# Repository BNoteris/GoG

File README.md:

# LoRa GPS IoT — PCB Proof-of-Concept

This repository hosts the LoRa GPS IoT proof-of-concept developed as the final project of the High Frequency Circuit Design course at ECAM.
The system integrates a GPS receiver, an ESP32 microcontroller, and a LoRa transceiver to provide location reporting over the LoRaWAN 868 MHz band.
A dedicated custom PCB antenna was designed, simulated and produced for LoRa operation at 868 MHz 
The design was specified in collaboration with an industrial partner and implemented on a 2‑layer FR4 PCB.
Every tool used during this project was open-source.

<div align="center">

</div>

All KiCad & gerber files are available in the [hardware](/hardware) directory.

Antenna simulation can be found in [software](/software).

## Specifications

- Provide GPS-based localization transmission over LoRa at the 868 MHz European LoRa frequency band.
- Support Wi-Fi/BLE communication with ESP32 provided antenna.
- Support multiple power inputs: USB‑C, external battery (2S), and solar panel input.
- Create a compact PCB (≤ 10×10 cm for fabrication on JLCPCB) as a proof of concept.
- Create a custom Inverted‑F Antenna (IFA) tuned to 868 MHz.

## Hardware used

- **ESP32‑C3‑WROOM‑02** — main MCU (USB‑C programming and Wi‑Fi/BLE). Supports SPI and I²C for peripheral interfaces.
- **RFM95 (LoRa) module** — 868 MHz LoRa transceiver (module used without on‑board antenna; external/custom antenna on separate antenna PCB).
- **GPS module AM‑M8Q‑0** — GNSS receiver for latitude/longitude acquisition.
- **BQ25798** — battery charger/power manager supporting USB‑C and solar inputs, designed for a 2S battery configuration.
- **USB‑C connector** — for programming and charging.
- **SMA connector** — RF connector for the custom antenna / external antenna.

## Antenna simulation & testing
### Simulation

Electromagnetic simulations were performed using the Emerge Python‑based EM tool to optimize the antenna geometry for maximum radiated power and minimal reflection at the target frequency.

 | 
:------------:|:--------------------------:
S11 reflection coefficient | Smith chart of reflection coefficient

Primary performance metrics from simulation:
- Minimum simulated **S₁₁ = −17.75 dB at 868 MHz**.
- **−10 dB impedance bandwidth ≈ 50 MHz**, which covers the LoRaWAN band with margin for manufacturing tolerances.

The simulated Smith chart shows the antenna impedance close to the center (near 50 Ω) at 868 MHz; minor adjustments were left open to address real‑world feed/feedline/environment effects.

 | 
:-----------:|:-------------------:
Far-Field E  |  Polar Far-Field E

<div align="center">

</div>

Far‑field results (normalized E‑field, polar plots and 3D radiation pattern) were generated to verify radiation behaviour

### Hardware validation

<div align="center">

</div>

The manufactured IFA PCB was integrated into the system and validated using a Digital Spectrum Analyzer (DSA) by observing a distinct spectral peak at 868 MHz aligned with the transmission cadence when our custom antenna is sending its packet to a reference antenna tuned to the same band.

 | 
:-------------------------------------------------:|:---------------------------------------------:
Spectrum analysis without custom antenna emission  | Spectrum analysis with custom antenna emission 

Results confirm that the antenna radiates at the intended operating frequency.
Minor nearby spectral peaks were attributed to ambient RF activity.

Limitations: a Vector Network Analyzer (VNA) was not available during testing, preventing direct measurement of the antenna reflection coefficient (S₁₁) on the manufactured part.
This measurement is recommended for a definitive comparison against simulation.

## Improvements

Several enhancements could be considered to further improve the system’s performance 
and quality: 
- As the PCB was intentionally designed with only 2 layers and no ground/power 
planes to observe and measure EMI, but has finally not been done, upgrading our 
design to 4 layers with copper planes would simplify the PCB layout and improve 
EMC. It would, consequently, allow for a more compact design, making it more 
practical.
- Testing our system to EMI interferences would allow to have a better knowledge of 
its real-world performance, as well as its capability to respect HF regulations, a 
mandatory step to deliver our product to the market. 
- Access to a Vector Network Analyzer (or even a LiteVNA) would enable precise 
measurements of the antenna reflection coefficient and matching impedance, 
allowing direct comparison with simulation results and more accurate impedance 
tuning. 
- Testing the system in a real-world environment would provide more information on 
its robustness, in particular, packet loss and communication range and 
performance.

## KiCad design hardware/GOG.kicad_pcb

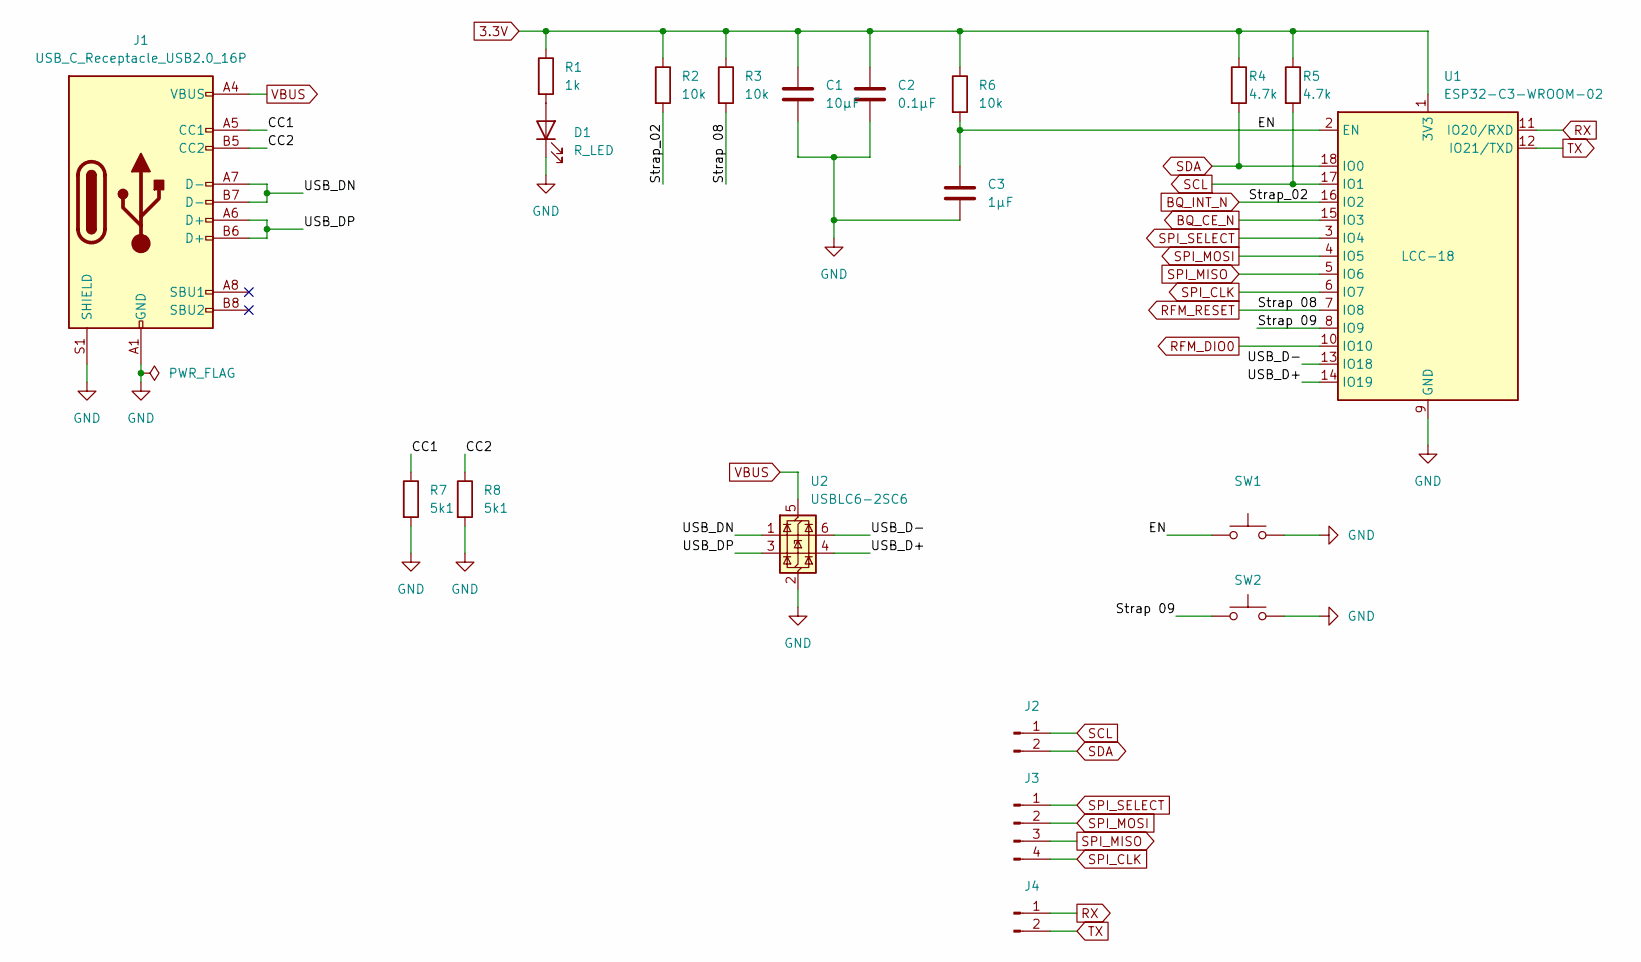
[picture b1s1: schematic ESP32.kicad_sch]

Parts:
C1: 10µF; C_0603_1608Metric; JLCPCB Part # C96446
C2: 0.1µF; C_0603_1608Metric; JLCPCB Part # C1590
C3: 1µF; C_0603_1608Metric; JLCPCB Part # C29936
D1: R_LED; LED_0603_1608Metric; JLCPCB Part # C7470862
J1: USB_C_Receptacle_USB2.0_16P; USB_C_Receptacle_GCT_USB4105-xx-A_16P_TopMnt_Horizontal; JLCPCB Part # C393939
J2, J4: Conn_01x02_Pin; PinHeader_1x02_P2.54mm_Vertical; JLCPCB Part # C7501260
J3: Conn_01x04_Pin; PinHeader_1x04_P2.54mm_Vertical; JLCPCB Part # C7501262
R1: 1k; R_0603_1608Metric; JLCPCB Part # C22548
R2, R3, R6: 10k; R_0603_1608Metric; JLCPCB Part # C98220
R4, R5: 4.7k; R_0603_1608Metric; JLCPCB Part # C99782
R7, R8: 5k1; R_0603_1608Metric; JLCPCB Part # C105580
SW1, SW2: SW_Omron_B3FS; SW_SPST_Omron_B3FS-101xP; JLCPCB Part # C231324
U1: ESP32-C3-WROOM-02; JLCPCB Part # C2934560
U2: USBLC6-2SC6; SOT-23-6; JLCPCB Part # C7519

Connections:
3.3V: C1.1, C2.1, R1.1, R2.1, R3.1, R4.1, R5.1, R6.1, U1.1 (3V3); also elsewhere on the board
/ESP32/CC1: J1.A5 (CC1), R7.1
/ESP32/CC2: J1.B5 (CC2), R8.1
/ESP32/EN: C3.1, R6.2, SW1.1, U1.2 (EN)
/ESP32/Strap 09: SW2.1, U1.8 (IO9)
/ESP32/USB_D+: U1.14 (IO19), U2.4 (I/O2)
/ESP32/USB_D-: U1.13 (IO18), U2.6 (I/O1)
/ESP32/USB_DN: J1.A7 (D-), J1.B7 (D-), U2.1 (I/O1)
/ESP32/USB_DP: J1.A6 (D+), J1.B6 (D+), U2.3 (I/O2)
BQ_CE_N: U1.15 (IO3); also elsewhere on the board
BQ_INT_N: R2.2, U1.16 (IO2); also elsewhere on the board
GND: C1.2, C2.2, C3.2, D1.1 (K), J1.A1 (GND), J1.A12 (GND), J1.B1 (GND), J1.B12 (GND), J1.S1 (SHIELD), R7.2, R8.2, SW1.2, SW2.2, U1.9 (GND), U1.19 (GND), U2.2 (GND); also elsewhere on the board
unnamed: D1.2 (A), R1.2
RFM_DIO0: U1.10 (IO10); also elsewhere on the board
RFM_RESET: R3.2, U1.7 (IO8); also elsewhere on the board
RX: J4.1, U1.11 (IO20/RXD)
SCL: J2.1, R5.2, U1.17 (IO1); also elsewhere on the board
SDA: J2.2, R4.2, U1.18 (IO0); also elsewhere on the board
SPI_CLK: J3.4, U1.6 (IO7); also elsewhere on the board
SPI_MISO: J3.3, U1.5 (IO6); also elsewhere on the board
SPI_MOSI: J3.2, U1.4 (IO5); also elsewhere on the board
SPI_SELECT: J3.1, U1.3 (IO4); also elsewhere on the board
TX: J4.2, U1.12 (IO21/TXD)
VBUS: J1.A4 (VBUS), J1.A9 (VBUS), J1.B4 (VBUS), J1.B9 (VBUS), U2.5 (VBUS); also elsewhere on the board

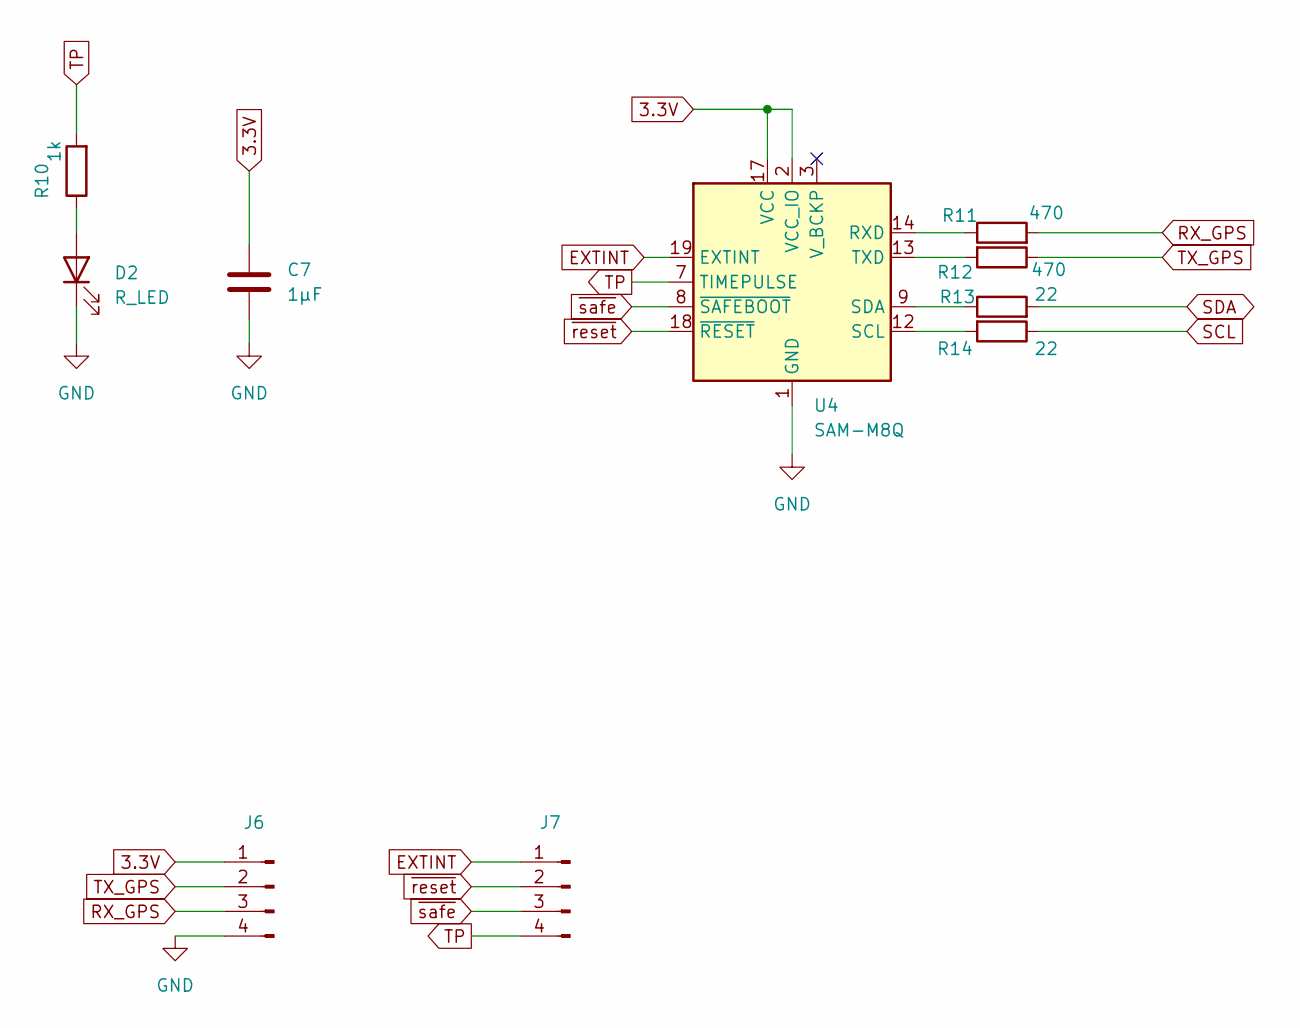
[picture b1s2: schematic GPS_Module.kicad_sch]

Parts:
C7: 1µF; C_0603_1608Metric; JLCPCB Part # C29936
D2: R_LED; LED_0603_1608Metric; JLCPCB Part # C7470862
J6, J7: Conn_01x04_Pin; JST_XH_B4B-XH-A_1x04_P2.50mm_Vertical; JLCPCB Part # C161871
R10: 1k; R_0603_1608Metric; JLCPCB Part # C22548
R11, R12: 470; R_0603_1608Metric; JLCPCB Part # C114669
R13, R14: 22; R_0603_1608Metric; JLCPCB Part # C107701
U4: SAM-M8Q; ublox_SAM-M8Q; JLCPCB Part # C5447387

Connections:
3.3V: C7.1, J6.1, U4.2 (VCC_IO), U4.17 (VCC); also elsewhere on the board
EXTINT: J7.1, U4.19 (EXTINT)
GND: C7.2, D2.1 (K), J6.4, U4.1 (GND), U4.4 (GND), U4.5 (GND), U4.6 (GND), U4.10 (GND), U4.11 (GND), U4.15 (GND), U4.16 (GND), U4.20 (GND); also elsewhere on the board
unnamed: D2.2 (A), R10.1
unnamed: R11.1, U4.14 (RXD)
unnamed: R14.2, U4.12 (SCL)
unnamed: R13.1, U4.9 (SDA)
unnamed: R12.2, U4.13 (TXD)
RX_GPS: J6.3, R11.2
SCL: R14.1; also elsewhere on the board
SDA: R13.2; also elsewhere on the board
TP: J7.4, R10.2, U4.7 (TIMEPULSE)
TX_GPS: J6.2, R12.1
~reset: J7.2, U4.18 (~RESET)
~safe: J7.3, U4.8 (~SAFEBOOT)

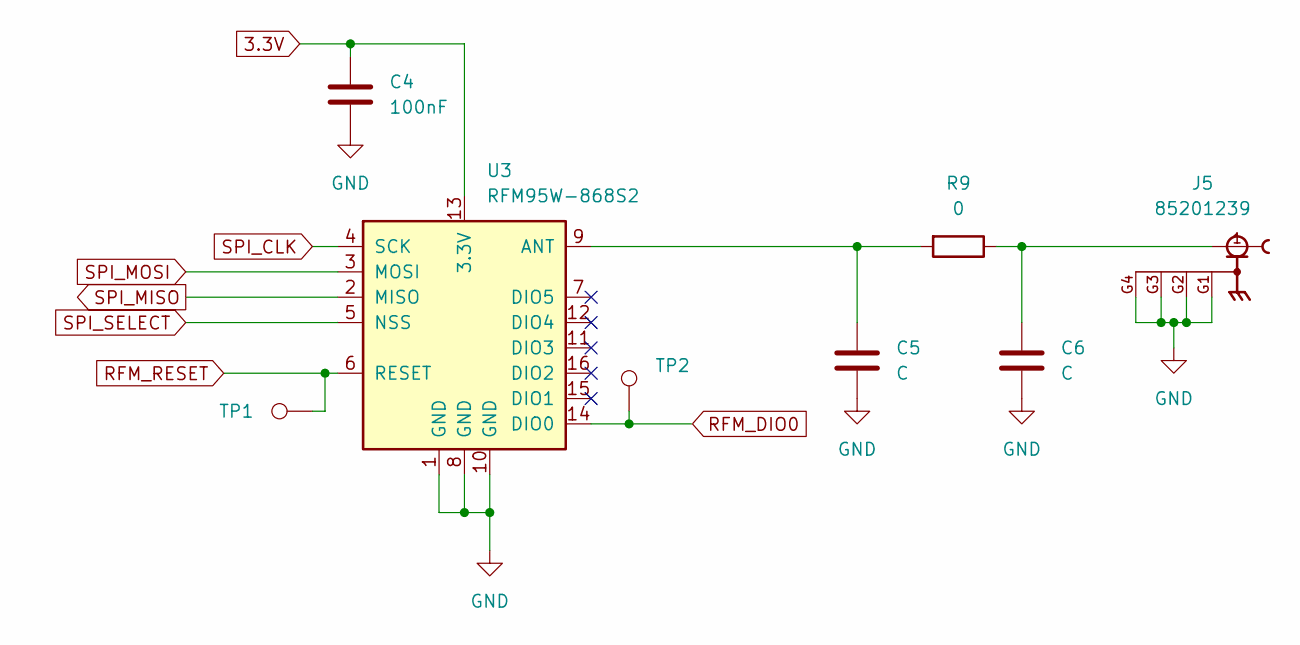
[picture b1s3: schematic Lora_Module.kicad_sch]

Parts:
C4: 100nF; C_0603_1608Metric; JLCPCB Part # C1590
C5, C6: C; R_0805_2012Metric_Pad1.20x1.40mm_HandSolder; JLCPCB Part # /
J5: 85201239; HUBER_SUHNER_85201239; PARTREV A; JLCPCB Part # C7498154
R9: 0; R_0805_2012Metric_Pad1.20x1.40mm_HandSolder; JLCPCB Part # /
TP1, TP2: TestPoint; TestPoint_Pad_D1.5mm_JLCPCB
U3: RFM95W-868S2; HOPERF_RFM9XW_SMD; JLCPCB Part # C2844472

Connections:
3.3V: C4.1, U3.13 (3.3V); also elsewhere on the board
GND: C4.2, C5.2, C6.2, J5.G1, J5.G2, J5.G3, J5.G4, U3.1 (GND), U3.8 (GND), U3.10 (GND); also elsewhere on the board
unnamed: C6.1, J5.1, R9.1
unnamed: C5.1, R9.2, U3.9 (ANT)
RFM_DIO0: TP2.1, U3.14 (DIO0); also elsewhere on the board
RFM_RESET: TP1.1, U3.6 (RESET); also elsewhere on the board
SPI_CLK: U3.4 (SCK); also elsewhere on the board
SPI_MISO: U3.2 (MISO); also elsewhere on the board
SPI_MOSI: U3.3 (MOSI); also elsewhere on the board
SPI_SELECT: U3.5 (NSS); also elsewhere on the board

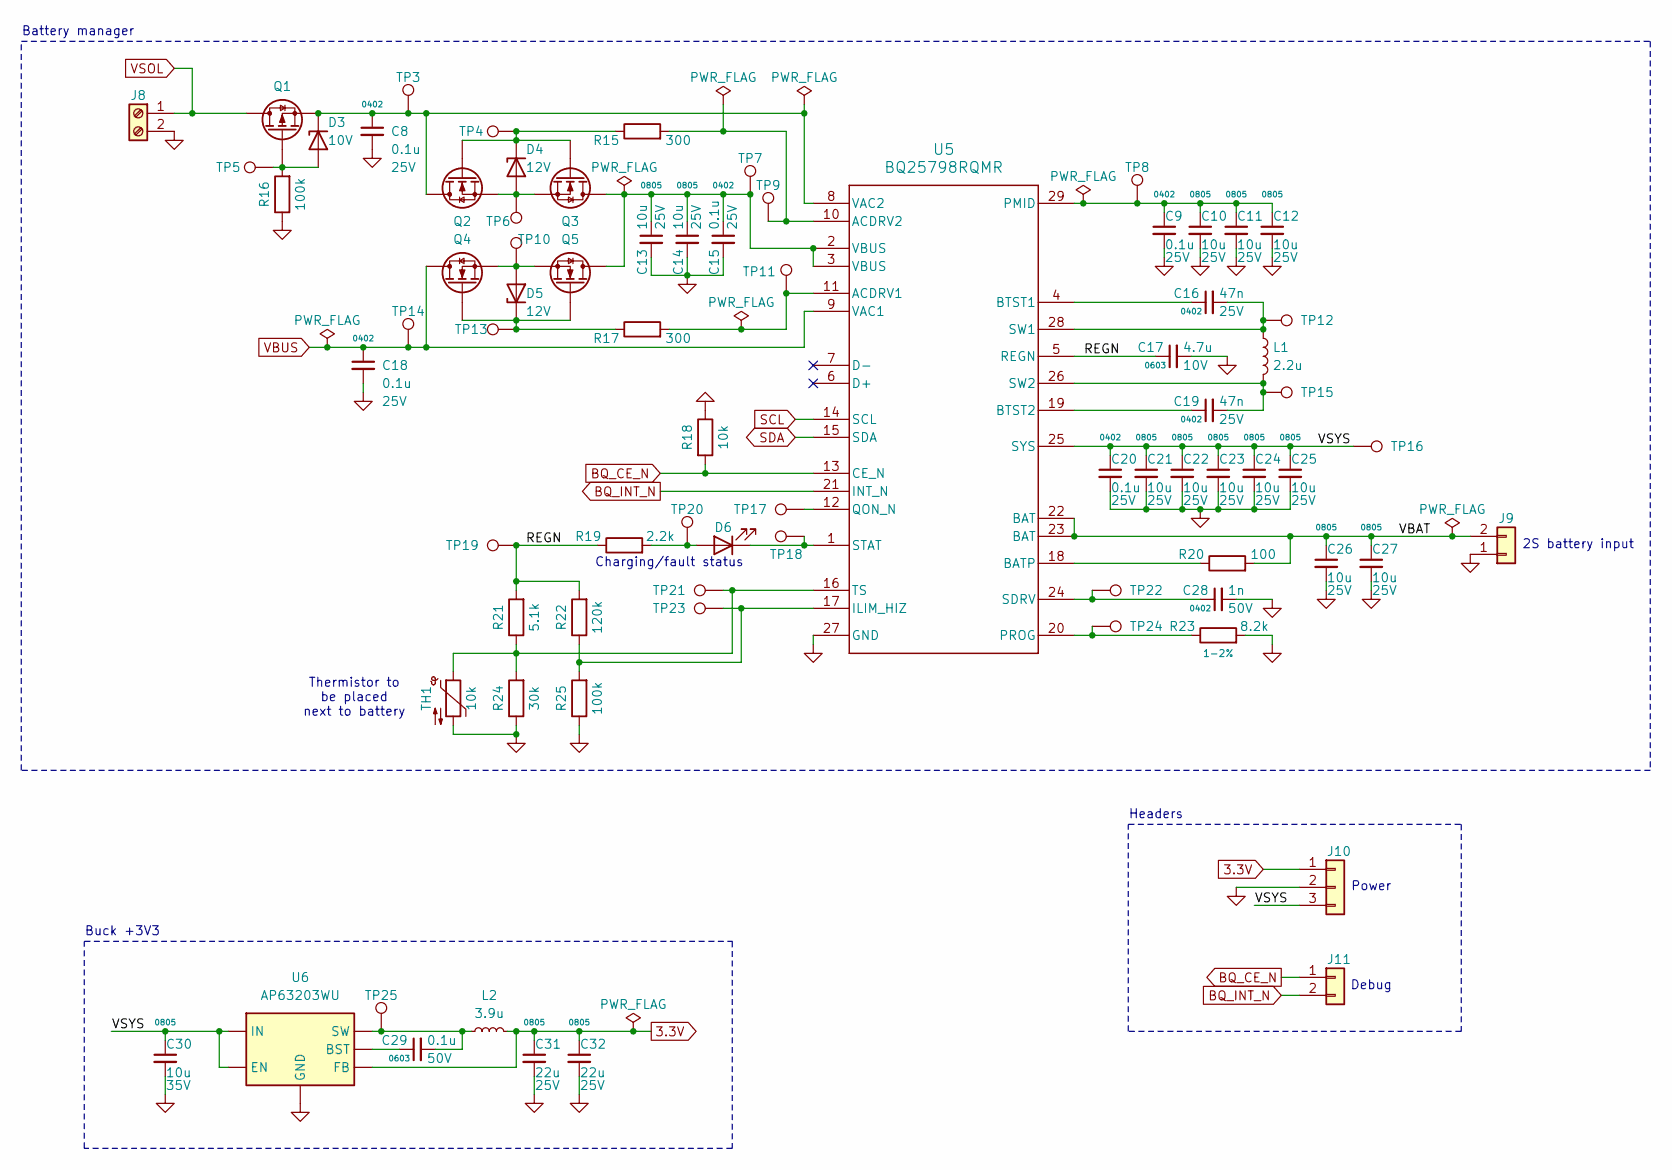
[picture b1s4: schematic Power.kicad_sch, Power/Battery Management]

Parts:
C8, C9, C15, C18, C20: 0.1u; C_0402_1005Metric_JLCPCB; Voltage 25V; JLCPCB Part # C100072
C10, C11, C12, C13, C14, C21, C22, C23, C24, C25, C26, C27: 10u; C_0805_2012Metric; Voltage 25V; JLCPCB Part # C15850
C16, C19: 47n; C_0402_1005Metric_JLCPCB; Voltage 25V; JLCPCB Part # C107020
C17: 4.7u; C_0603_1608Metric; Voltage 10V; JLCPCB Part # C1705
C28: 1n; C_0402_1005Metric_JLCPCB; Voltage 50V; JLCPCB Part # C14442
C29: 0.1u; C_0603_1608Metric; Voltage 50V; JLCPCB Part # C14663
C30: 10u; C_0805_2012Metric; Voltage 35V; JLCPCB Part # C33546007
C31, C32: 22u; C_0805_2012Metric; Voltage 25V; JLCPCB Part # C45783
D3: D_Zener; D_SOD-123; Voltage 10V; JLCPCB Part # C48870
D4, D5: D_Zener; D_SOD-123; Voltage 12V; JLCPCB Part # C97772
D6: LED; LED_0603_1608Metric; JLCPCB Part # C7470862
J8: Screw_Terminal_01x02; TerminalBlock_WJ126V-5.0-2P_1x02_P5.00mm; JLCPCB Part # C8404
J9: Conn_01x02; JST_XH_B2B-XH-A_1x02_P2.50mm_Vertical; JLCPCB Part # C158012
J10: Conn_01x03; PinHeader_1x03_P2.54mm_Vertical; JLCPCB Part # C7501261
J11: Conn_01x02; PinHeader_1x02_P2.54mm_Vertical; JLCPCB Part # C7501260
L1: 2.2u; MDA5030-2R2M; JLCPCB Part # C2847475
L2: 3.9u; L_Sunlord_SWPA4030S; JLCPCB Part # C96899
Q1: Q_PMOS; SOT-23; JLCPCB Part # C5350989
Q2, Q3, Q4, Q5: Q_NMOS; SOT-23; JLCPCB Part # C2938367
R15, R17: 300; R_0603_1608Metric; JLCPCB Part # C114617
R16, R25: 100k; R_0402_1005Metric_JLCPCB; JLCPCB Part # C60491
R18: 10k; R_0402_1005Metric_JLCPCB; JLCPCB Part # C60490
R19: 2.2k; R_0402_1005Metric_JLCPCB; JLCPCB Part # C163447
R20: 100; R_0402_1005Metric_JLCPCB; JLCPCB Part # C106232
R21: 5.1k; R_0402_1005Metric_JLCPCB; JLCPCB Part # C105872
R22: 120k; R_0402_1005Metric_JLCPCB; JLCPCB Part # C93945
R23: 8.2k; R_0402_1005Metric_JLCPCB; Tolerence 1-2%; JLCPCB Part # C137929
R24: 30k; R_0402_1005Metric_JLCPCB; JLCPCB Part # C138008
TH1: 10k; Thermistor NTC
TP3, TP4, TP5, TP6, TP7, TP8, TP9, TP10, TP11, TP12, TP13, TP14, TP15, TP16, TP17, TP18, TP19, TP20, TP21, TP22, TP23, TP24, TP25: TestPoint; TestPoint_Pad_D1.5mm_JLCPCB
U5: BQ25798RQMR; IC_BQ25798RQMR; JLCPCB Part # C2876593
U6: AP63203WU; TSOT-23-6; JLCPCB Part # C780769

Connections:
3.3V: C31.1, C32.1, J10.1, L2.2, U6.1 (FB); also elsewhere on the board
/Power/REGN: C17.1, R19.1, R21.2, R22.2, TP19.1, U5.5 (REGN)
/Power/VBAT: C26.1, C27.1, J9.2, R20.2, U5.22 (BAT), U5.23 (BAT)
/Power/VSYS: C20.1, C21.1, C22.1, C23.1, C24.1, C25.1, C30.1, J10.3, TP16.1, U5.25 (SYS), U6.2 (EN), U6.3 (IN)
BQ_CE_N: J11.1, R18.2, U5.13 (CE_N); also elsewhere on the board
BQ_INT_N: J11.2, U5.21 (INT_N); also elsewhere on the board
GND: C8.2, C9.2, C10.2, C11.2, C12.2, C13.2, C14.2, C15.2, C17.2, C18.2, C20.2, C21.2, C22.2, C23.2, C24.2, C25.2, C26.2, C27.2, C28.2, C30.2, C31.2, C32.2, J8.2, J9.1, J10.2, R16.1, R18.1, R23.2, R24.1, R25.1, TH1.2, U5.27 (GND), U6.4 (GND); also elsewhere on the board
unnamed: D3.2 (A), Q1.1 (G), R16.2, TP5.1
unnamed: C8.1, D3.1 (K), Q1.2 (S), Q2.3 (D), TP3.1, U5.8 (VAC2)
unnamed: D4.2 (A), Q2.2 (S), Q3.2 (S), TP6.1
unnamed: D4.1 (K), Q2.1 (G), Q3.1 (G), R15.1, TP4.1
unnamed: D5.2 (A), Q4.2 (S), Q5.2 (S), TP10.1
unnamed: D5.1 (K), Q4.1 (G), Q5.1 (G), R17.1, TP13.1
unnamed: D6.2 (A), R19.2, TP20.1
unnamed: D6.1 (K), TP18.1, U5.1 (STAT)
unnamed: C13.1, C14.1, C15.1, Q3.3 (D), Q5.3 (D), TP7.1, U5.2 (VBUS), U5.3 (VBUS)
unnamed: R17.2, TP11.1, U5.11 (ACDRV1)
unnamed: R15.2, TP9.1, U5.10 (ACDRV2)
unnamed: R20.1, U5.18 (BATP)
unnamed: C16.1, U5.4 (BTST1)
unnamed: C19.1, U5.19 (BTST2)
unnamed: R22.1, R25.2, TP23.1, U5.17 (ILIM_HIZ)
unnamed: C9.1, C10.1, C11.1, C12.1, TP8.1, U5.29 (PMID)
unnamed: R23.1, TP24.1, U5.20 (PROG)
unnamed: TP17.1, U5.12 (QON_N)
unnamed: C28.1, TP22.1, U5.24 (SDRV)
unnamed: C16.2, L1.1, TP12.1, U5.28 (SW1)
unnamed: C19.2, L1.2, TP15.1, U5.26 (SW2)
unnamed: R21.1, R24.2, TH1.1, TP21.1, U5.16 (TS)
unnamed: C29.1, U6.6 (BST)
unnamed: C29.2, L2.1, TP25.1, U6.5 (SW)
SCL: U5.14 (SCL); also elsewhere on the board
SDA: U5.15 (SDA); also elsewhere on the board
VBUS: C18.1, Q4.3 (D), TP14.1, U5.9 (VAC1); also elsewhere on the board
VSOL: J8.1, Q1.3 (D)

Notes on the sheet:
Debug
Buck +3V3
Headers
Thermistor to be placed next to battery
Charging/fault status
2S battery input
Power
Battery manager

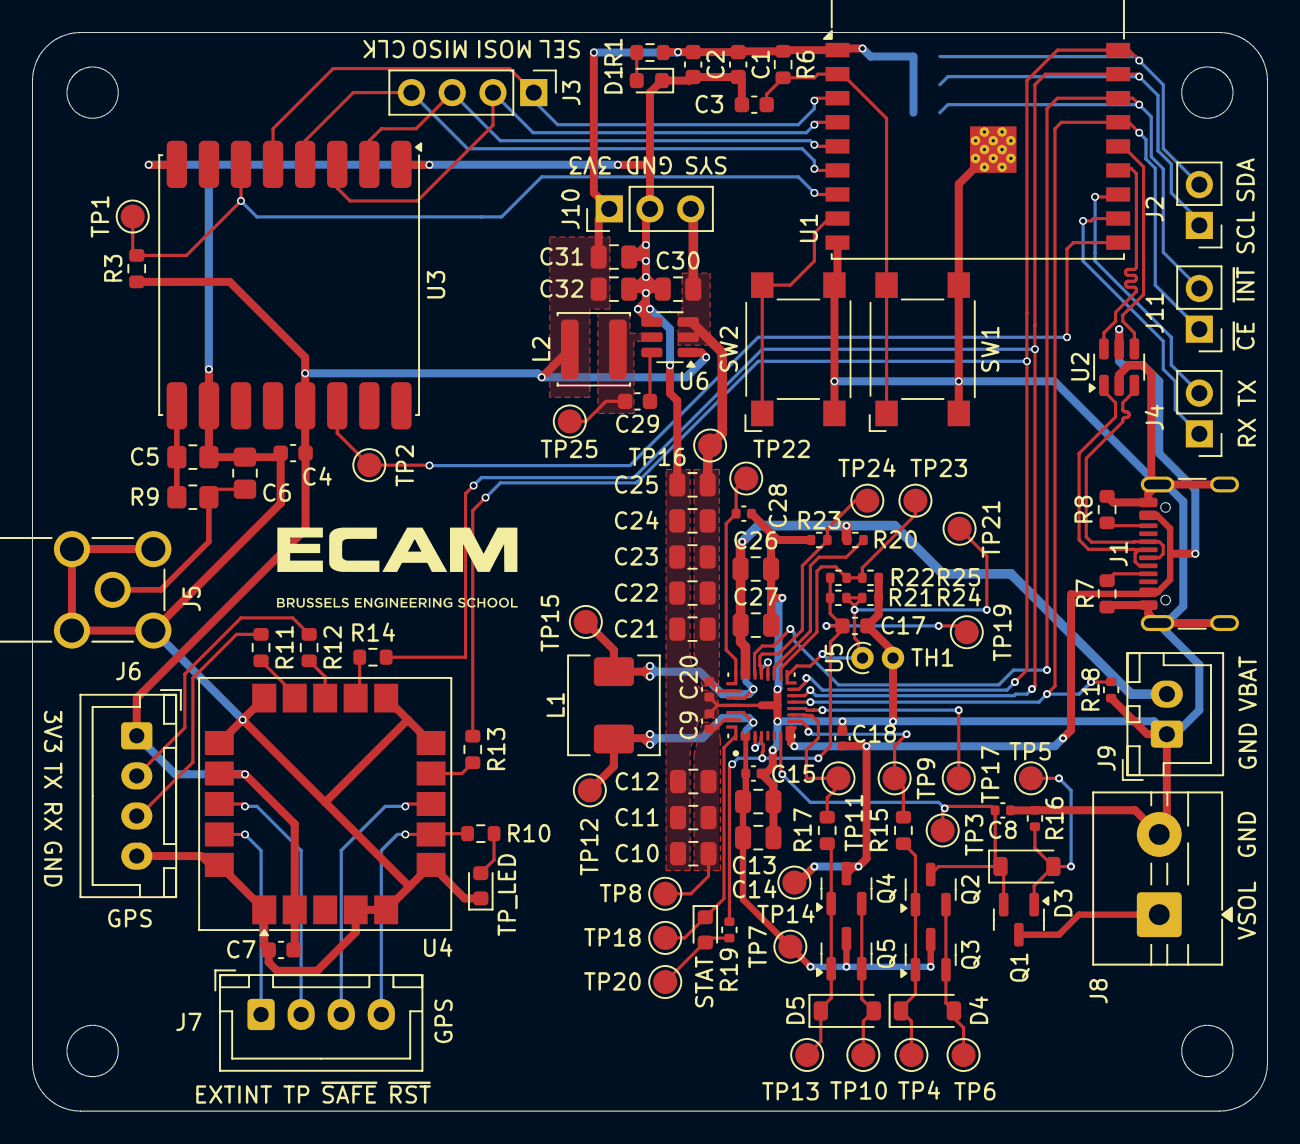
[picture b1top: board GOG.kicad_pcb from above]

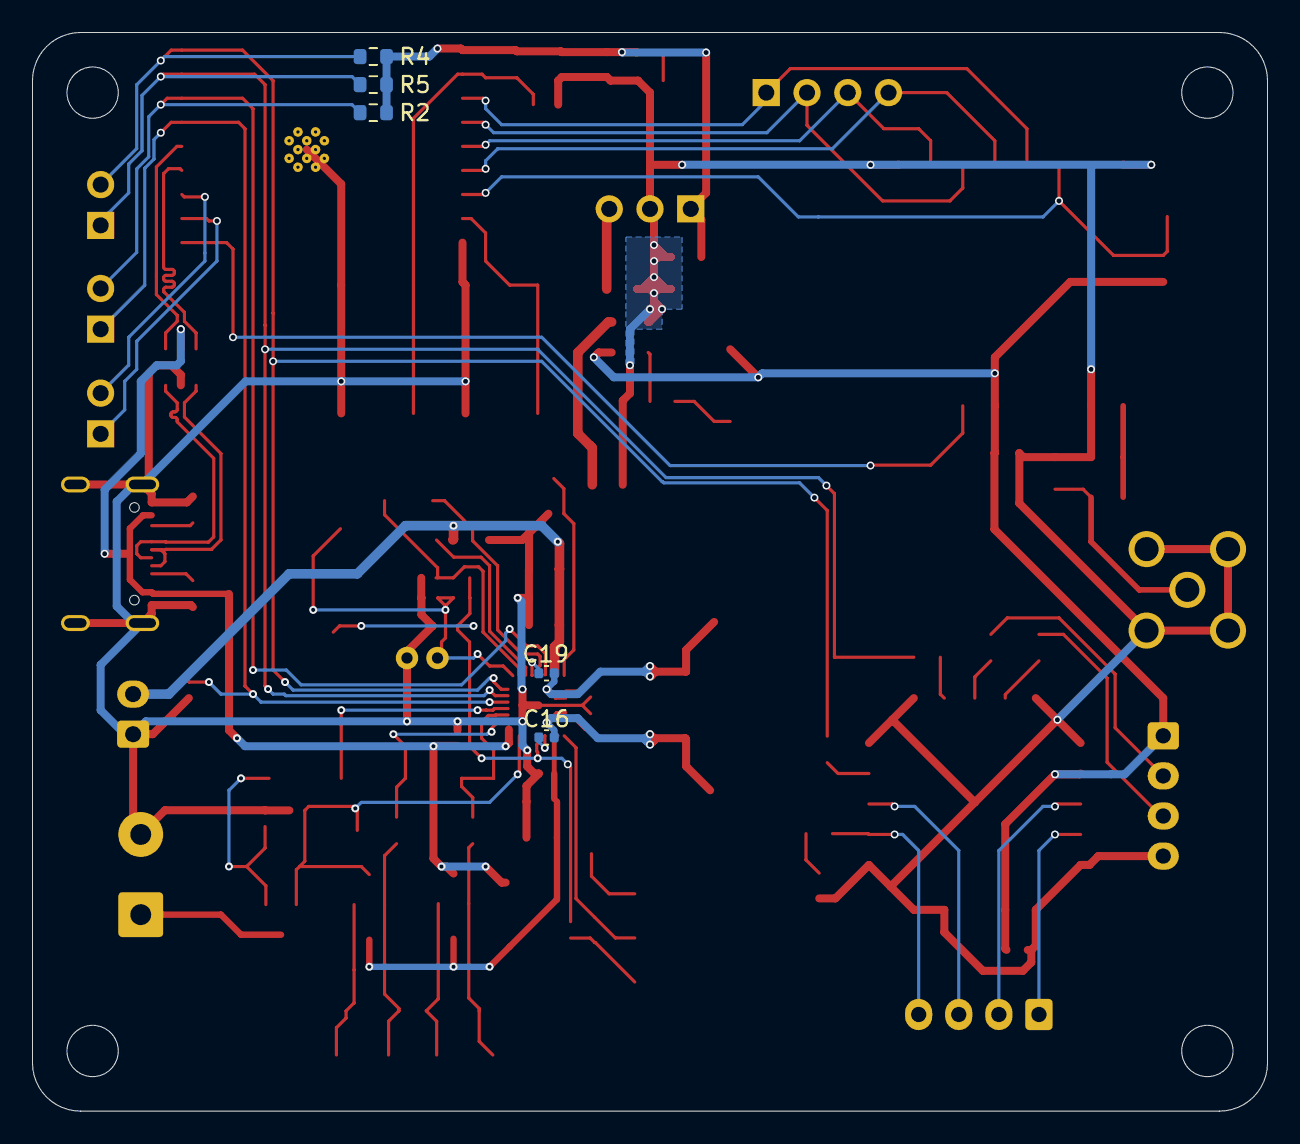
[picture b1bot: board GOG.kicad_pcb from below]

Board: 2 copper layers, 77.0 x 67.2 mm, 115 parts (5 on the bottom side), 65 nets.

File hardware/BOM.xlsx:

Reference | Value | Footprint | Description | Qty | JLCPCB Part # | Package
C1 | 10µF | Capacitor_SMD:C_0603_1608Metric | CL10A106MA8NRNC 10uF 25V X5R ±20% 0603 Multilayer Ceramic Capacitor | 1 | C96446 | 0603
C10,C11,C12,C13,C14,C21,C22,C23,C24,C25,C26,C27 | 10u | Capacitor_SMD:C_0805_2012Metric | CL21A106KAYNNNE 10uF 25V X5R ±10% 0805 Multilayer Ceramic Capacitor | 12 | C15850 | 0805
C16,C19 | 47n | GoG_Library:C_0402_1005Metric_JLCPCB | CC0402KRX7R8BB473 25V 47nF X7R ±10% 0402 Multilayer Ceramic Capacitor | 2 | C107020 | 0402
C17 | 4.7u | Capacitor_SMD:C_0603_1608Metric | CL10A475KP8NNNC 10V 4.7uF X5R ±10% 0603 Multilayer Ceramic Capacitor | 1 | C1705 | 0603
C2 | 0.1µF | Capacitor_SMD:C_0603_1608Metric | CL10B104KA8NNNC 100nF 25V X7R ±10% 0603 Multilayer Ceramic Capacitors MLCC - SM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 | 1 | C1590 | 0603
C28 | 1n | GoG_Library:C_0402_1005Metric_JLCPCB | CL05B102KB5NNNC 1nF 50V X7R ±10% 0402 Multilayer Ceramic Capacitor | 1 | C14442 | 0402
C29 | 0.1u | Capacitor_SMD:C_0603_1608Metric | CC0603KRX7R9BB104 100nF 50V X7R ±10% 0603 Multilayer Ceramic Capacitor | 1 | C14663 | 0603
C3,C7 | 1µF | Capacitor_SMD:C_0603_1608Metric | CL10B105KA8NNNC 1uF 25V X7R ±10% 0603 Multilayer Ceramic Capacitor | 2 | C29936 | 0603
C30 | 10u | Capacitor_SMD:C_0805_2012Metric | HGC0805R5106K350NSLJ 10uF 35V X5R ±10% 0805 Multilayer Ceramic Capacitor | 1 | C33546007 | 0805
C31,C32 | 22u | Capacitor_SMD:C_0805_2012Metric | CL21A226MAQNNNE 22uF 25V X5R ±20% 0805 Multilayer Ceramic Capacitor | 2 | C45783 | 0805
C4 | 100nF | Capacitor_SMD:C_0603_1608Metric | CL10B104KA8NNNC 100nF 25V X7R ±10% 0603 Multilayer Ceramic Capacitors MLCC - SM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 | 1 | C1590 | 0603
C5,C6 | (NC) | Resistor_SMD:R_0805_2012Metric_Pad1.20x1.40mm_HandSolder | Unpolarized capacitor | 2 | / | 0805 | Non connect capacitors for antenna : Remove from assembly BOM
C8,C9,C15,C18,C20 | 0.1u | GoG_Library:C_0402_1005Metric_JLCPCB | CL05A104KA5NNNC 100nF 25V X5R ±10% 0402 Multilayer Ceramic Capacitor | 5 | C100072 | 0402
D1,D2 | R_LED | LED_SMD:LED_0603_1608Metric | MEIHUA MHT192DUGCT LED 2.3V~2.8V 518nm 565mcd 5mA 60mW Green | 2 | C7470862 | 0603
D3 | D_Zener | Diode_SMD:D_SOD-123 | ONSEMI MMSZ4697T1G Zener diode 10V 1uA@7.6V 500mW 9.5V~10.5V | 1 | C48870 | SOD-123
D4,D5 | D_Zener | Diode_SMD:D_SOD-123 | ONSEMI MMSZ4699T1G Zener diode 12V 500mW 50nA@9.1V | 2 | C97772 | SOD-123
D6 | LED | LED_SMD:LED_0603_1608Metric | MEIHUA MHT192DUGCT LED 2.3V~2.8V 518nm 565mcd 5mA 60mW Green | 1 | C7470862 | 0603
J1 | USB_C_Receptacle_USB2.0_16P | Connector_USB:USB_C_Receptacle_GCT_USB4105-xx-A_16P_TopMnt_Horizontal | TYPE-C16PIN USB 2.0-only 16P Type-C Receptacle connector | 1 | C393939 | SMD
J10 | Conn_01x03 | Connector_PinHeader_2.54mm:PinHeader_1x03_P2.54mm_Vertical | ZX-PZ2.54-1-3PZZ 1x3P 2.54mm Pin Header | 1 | C7501261 | Plugin,P=2.54mm
J11 | Conn_01x02 | Connector_PinHeader_2.54mm:PinHeader_1x02_P2.54mm_Vertical | ZX-PZ2.54-1-2PZZ 1x2P 2.54mm Pin Header | 1 | C7501260 | Plugin,P=2.54mm
J2,J4 | Conn_01x02_Pin | Connector_PinHeader_2.54mm:PinHeader_1x02_P2.54mm_Vertical | ZX-PZ2.54-1-2PZZ 1x2P 2.54mm Pin Header | 2 | C7501260 | Plugin,P=2.54mm
J3 | Conn_01x04_Pin | Connector_PinHeader_2.54mm:PinHeader_1x04_P2.54mm_Vertical | ZX-PZ2.54-1-4PZZ 1x4P 2.54mm Pin Header | 1 | C7501262 | Plugin,P=2.54mm
J5 | 85201239 | SMA-85201239:HUBER_SUHNER_85201239 | -45℃~+80℃ 1 14.6mm 4.65mm 50Ω 6GHz Board Side Inner Bore Plugin Coaxial Connect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 | 1 | C7498154 | Plugin
J6,J7 | Conn_01x04_Pin | Connector_JST:JST_XH_B4B-XH-A_1x04_P2.50mm_Vertical | B4B-XH-AM(LF)(SN) 1x4P 2.5mm JST connector | 2 | C161871 | Plugin,P=2.5mm
J8 | Screw_Terminal_01x02 | GoG_Library:TerminalBlock_WJ126V-5.0-2P_1x02_P5.00mm | WJ126V-5.0-2P 1x2P P=5mm Screw Terminal Block | 1 | C8404 | Plugin,P=5mm
J9 | Conn_01x02 | Connector_JST:JST_XH_B2B-XH-A_1x02_P2.50mm_Vertical | B2B-XH-A(LF)(SN) 1x2P P=2.5mm XH JST connector | 1 | C158012 | Plugin,P=2.5mm
L1 | 2.2u | GoG_Library:MDA5030-2R2M | MDA5030-2R2M Inductor 2.2uH 21.6mΩ 6.5A 6.5A ±20% SMD, 5.7x5.2mm | 1 | C2847475 | SMD, 5.7x5.2mm
L2 | 3.9u | Inductor_SMD:L_Sunlord_SWPA4030S | SWPA4030S3R9MT 2.1A 3.9uH 3A 74mΩ ±20% SMD,4x4mm Power Inductor | 1 | C96899 | SMD, 4x4mm
Q1 | Q_PMOS | Package_TO_SOT_SMD:SOT-23 | P-MOSFET transistor | 1 | C5350989 | SOT-23
Q2,Q3,Q4,Q5 | Q_NMOS | Package_TO_SOT_SMD:SOT-23 | N-MOSFET transistor | 4 | C2938367 | SOT-23
R1,R10 | 1k | Resistor_SMD:R_0603_1608Metric | RC0603FR-071KL 100mW 1kΩ 75V Thick Film Resistor ±1% 0603 | 2 | C22548 | 0603
R11,R12 | 470 | Resistor_SMD:R_0603_1608Metric | RC0603FR-07470RL 100mW 470Ω 75V Thick Film Resistor ±1% 0603 | 2 | C114669 | 0603
R13,R14 | 22 | Resistor_SMD:R_0603_1608Metric | RC0603FR-0722RL 100mW 22Ω 75V Thick Film Resistor ±1% 0603 | 2 | C107701 | 0603
R15,R17 | 300 | Resistor_SMD:R_0603_1608Metric | RC0603FR-07300RL -55℃~+155℃ 100mW 300Ω 75V Thick Film Resistor ±1% ±100ppm/℃ 06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 | 2 | C114617 | 0603
R16,R25 | 100k | GoG_Library:R_0402_1005Metric_JLCPCB | RC0402FR-07100KL -55℃~+155℃ 100kΩ 50V 62.5mW Thick Film Resistor ±1% ±100ppm/℃ 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 | 2 | C60491 | 0402
R18 | 10k | GoG_Library:R_0402_1005Metric_JLCPCB | RC0402FR-0710KL -55℃~+155℃ 10kΩ 50V 62.5mW Thick Film Resistor ±1% ±100ppm/℃ 04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 | 1 | C60490 | 0402
R19 | 2.2k | GoG_Library:R_0402_1005Metric_JLCPCB | RC0402JR-072K2L -55℃~+155℃ 2.2kΩ 50V 62.5mW Thick Film Resistor ±100ppm/℃ ±5% 0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 | 1 | C163447 | 0402
R2,R3,R6 | 10k | Resistor_SMD:R_0603_1608Metric | RC0603FR-0710KL 100mW 10kΩ 75V Thick Film Resistor ±1% 0603 | 3 | C98220 | 0603
R20 | 100 | GoG_Library:R_0402_1005Metric_JLCPCB | RC0402FR-07100RL -55℃~+155℃ 100Ω 50V 62.5mW Thick Film Resistor ±1% ±100ppm/℃ 0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 | 1 | C106232 | 0402
R21 | 5.1k | GoG_Library:R_0402_1005Metric_JLCPCB | RC0402FR-075K1L -55℃~+155℃ 5.1kΩ 50V 62.5mW Thick Film Resistor ±1% ±100ppm/℃ 0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 | 1 | C105872 | 0402
R22 | 120k | GoG_Library:R_0402_1005Metric_JLCPCB | RC0402FR-07120KL -55℃~+155℃ 120kΩ 50V 62.5mW Thick Film Resistor ±1% ±100ppm/℃ 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 | 1 | C93945 | 0402
R23 | 8.2k | GoG_Library:R_0402_1005Metric_JLCPCB | RC0402FR-078K2L -55℃~+155℃ 50V 62.5mW 8.2kΩ Thick Film Resistor ±1% ±100ppm/℃ 0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 | 1 | C137929 | 0402
R24 | 30k | GoG_Library:R_0402_1005Metric_JLCPCB | RC0402FR-0730KL -55℃~+155℃ 30kΩ 50V 62.5mW Thick Film Resistor ±1% ±100ppm/℃ 04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 | 1 | C138008 | 0402
R4,R5 | 4.7k | Resistor_SMD:R_0603_1608Metric | RC0603FR-074K7L 100mW 4.7kΩ 75V Thick Film Resistor ±1% 0603 | 2 | C99782 | 0603
R7,R8 | 5k1 | Resistor_SMD:R_0603_1608Metric | RC0603FR-075K1L 100mW 5.1kΩ 75V Thick Film Resistor ±1% 0603 | 2 | C105580 | 0603
R9 | 0 | Resistor_SMD:R_0805_2012Metric_Pad1.20x1.40mm_HandSolder | PMR10EZPJ000 0Ω 500mW Shunt Resistor 0805 | 1 | C2842889 | 0805
SW1,SW2 | SW_Omron_B3FS | Button_Switch_SMD:SW_SPST_Omron_B3FS-101xP | Omron B3FS-1010P 6x6mm single pole normally-open tactile switch | 2 | C231324 | SMD-4P,6.3x6mm
TH1 | 10k | GoG_Library:Thermistor NTC | Vishay NTCLE413E2103F102L NTC Thermistor 10k 3435K | 1 | - | - | Get from Farnell : 2492885
U1 | ESP32-C3-WROOM-02 | RF_Module:ESP32-C3-WROOM-02 | 802.11 b/g/n Wi­Fi and Bluetooth 5 module, ESP32­C3 SoC, RISC­V microprocessor,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 | 1 | C2934560 | LCC-18
U2 | USBLC6-2SC6 | Package_TO_SOT_SMD:SOT-23-6 | USBLC6-2SC6 Very low capacitance ESD protection diode, 2 data-line, SOT-23-6 | 1 | C7519 | SOT-23-6L
U3 | RFM95W-868S2 | GoG_Library:HOPERF_RFM9XW_SMD | Low power long range transceiver module, SPI and parallel interface, 868 MHz, s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 | 1 | C2844472 | SMD,16x16mm
U4 | SAM-M8Q | RF_GPS:ublox_SAM-M8Q | GPS ublox M8 variant | 1 | C5447387 | SMD-20P,15x15mm | Out of stock
U5 | BQ25798RQMR | BQ25798RQMR:IC_BQ25798RQMR | -40℃~+85℃ 17uA 1~4 3.6V~24V 5A Charging IC I2C Lithium Battery Support QFN-29(4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 | 1 | C2876593 | QFN-29(4x4) | Out of stock
U6 | AP63203WU | Package_TO_SOT_SMD:TSOT-23-6 | 2A, 1.1MHz Buck DC/DC Converter, fixed 3.3V output voltage, TSOT-23-6 | 1 | C780769 | TSOT-23-6

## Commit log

2025-09-24 First commit -- datasheets
2025-09-24 esp32
2025-09-24 start_GPS
2025-09-24 Create .gitignore for KiCad project
    Add a .gitignore file for KiCad project files and temporary files.
2025-09-24 test
2025-09-24 Update project structure
2025-09-26 New usb port
2025-09-26 Main modules added + Com lines
2025-09-28 Basic 2 inputs source battery charger
2025-10-02 Pull up resistor i2c
2025-10-02 GPS schematic + datasheet
2025-10-02 ESL protection modification with usblc6 2sc6
2025-10-02 Change of esp32 footprint for wifi antenna
2025-10-06 Added BQ25798 integrated buck-boost inductor
2025-10-06 Added solar input protection & diodes footprints
2025-10-06 Updated BQ25798 pins location
2025-10-06 Add SYS output capacitors & cap. package sizes
2025-10-06 Add 2S battery circuit
2025-10-06 Added IN current limit & switching freq
2025-10-06 Created project library & MDA5030-2R2M footprint
2025-10-06 Add BQ25798 debug pins to ESP and placed TP & headers
2025-10-06 Add shunt resistor current sensing to solar input
2025-10-07 Added battery NTC thermistor footprint
2025-10-07 Started 5V/3.3V buck & add components to lib
2025-10-11 Finished 3.3V/5V buck design
2025-10-13 Made symbol space for capacitors
2025-10-13 Found all capacitors & inductors footprint & JLCPCB
2025-10-13 Found all resistors & pin headers footprint & JLCPCB
2025-10-14 Found all diodes & transistors footprint & JLCPCB
2025-10-14 Add JLCPCB Design Rules
2025-10-16 Module Lora
2025-10-16 Update ESP32 pins
2025-10-17 Ref composant JLCBPCB LoRa
2025-10-17 First draft
2025-10-18 Setup PCB design parameters
2025-10-18 Fix schematic components annotations
2025-10-18 Fix all ERC errors
2025-10-18 Fix several DRC errors & add all 3D models
2025-10-19 Finished battery manager placement
2025-10-19 Created ECAM logo as footprint
2025-10-19 Finished optimal placement & adapted/fixed schematic
2025-10-19 design v1
2025-10-19 text for power pins add
2025-10-19 Finished PCB routing
2025-10-20 Find all remaining components on JLCPCB
2025-10-20 Gerber fabrication outputs
2025-11-26 Add inverted F antenna simulation
2025-12-12 Ctreated very basic BQ25798 class
2025-12-17 brouillon
2025-12-17 Fix ESP to RFM95 pins
2025-12-17 Changed LoRa packet sending rate from 10s to 5s
2025-12-17 Fix SPI pins blocking communication to LoRa module
2026-01-19 Created README with project results
    Added detailed project description, specifications, hardware used, antenna simulation, and validation results.
